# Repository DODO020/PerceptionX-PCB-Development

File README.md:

PerceptionX PCB development repository

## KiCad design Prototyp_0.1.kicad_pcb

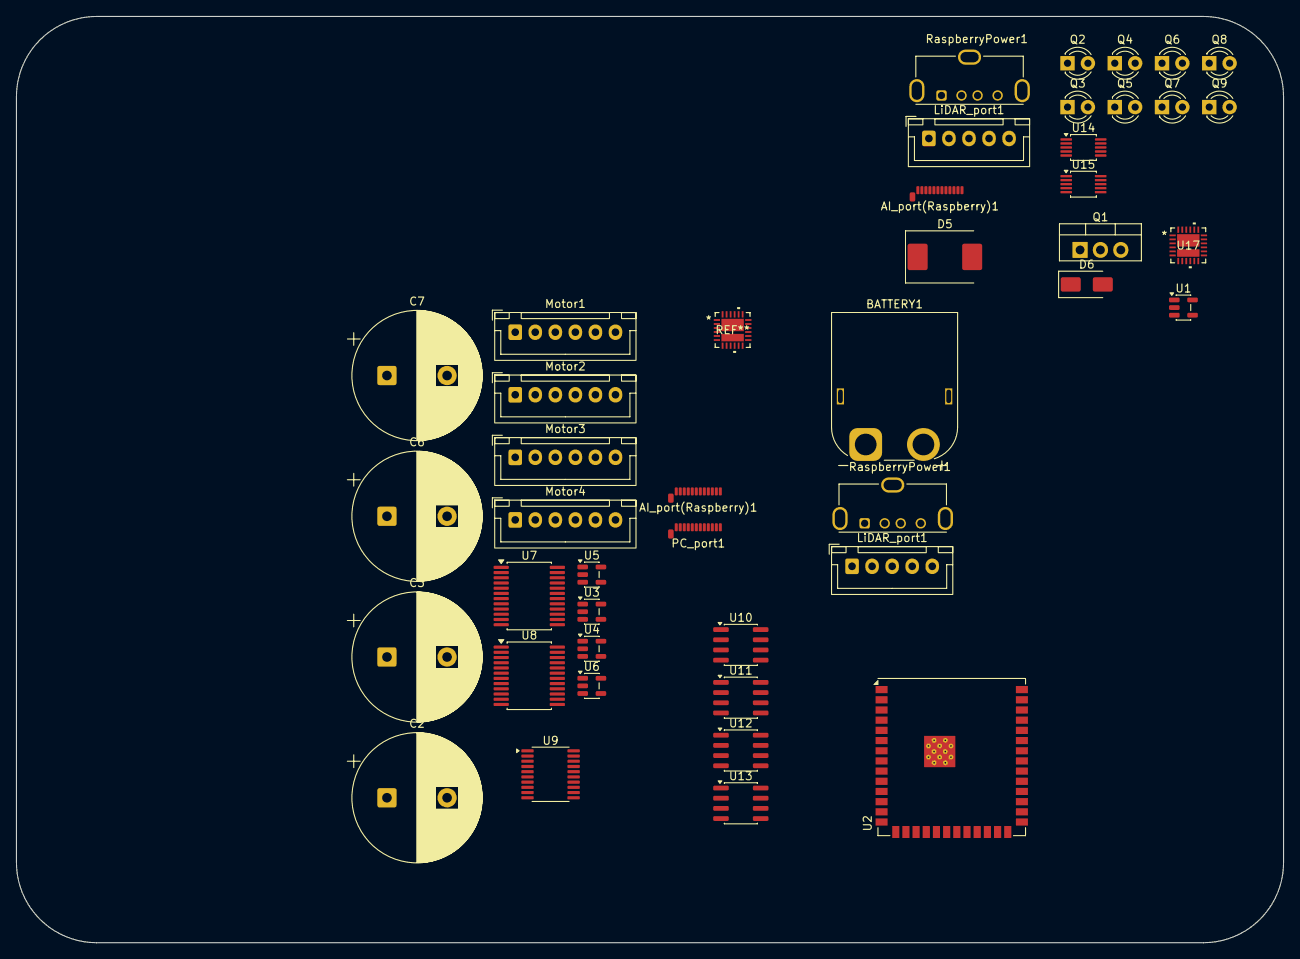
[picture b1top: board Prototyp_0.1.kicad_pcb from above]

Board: 2 copper layers, 158.0 x 115.5 mm, 43 parts (0 on the bottom side), 56 nets, no tracks yet.

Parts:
AI_port(Raspberry)1, AI_port(Raspberry)1#2: USB_C_Plug_USB2.0; USB_C_Plug_Molex_105444
BATTERY1: Conn_01x02; AMASS_XT60PW-M_1x02_P7.20mm_Horizontal
C2, C3: 10uF; CP_Radial_D16.0mm_P7.50mm
C6, C7: 220uF; CP_Radial_D16.0mm_P7.50mm
D5: 1.5SMCxxCA; D_SMC
D6: SS34; D_SMA
LiDAR_port1, LiDAR_port1#2: Conn_01x05; JST_XH_B5B-XH-A_1x05_P2.50mm_Vertical
Motor1, Motor2, Motor3, Motor4: Conn_01x06; JST_XH_B6B-XH-A_1x06_P2.50mm_Vertical
PC_port1: USB_C_Plug_USB2.0; USB_C_Plug_Molex_105444
Q1: IRLB8721PBF; TO-220-3_Vertical
Q2, Q3, Q4, Q5, Q6, Q7, Q8, Q9: SFH309; LED_D3.0mm_Clear
RaspberryPower1, RaspberryPower1#2: USB_A; USB_A_Molex_105057_Vertical
U1: XC6220B331MR; SOT-23-5
U2: ESP32-S3-WROOM-1U
U3, U4, U5, U6: 74LVC1G04; SOT-23-5
U7, U8: TB6612FNG; SSOP-24_5.3x8.2mm_P0.65mm
U9: PCF8574TS; SSOP-20_4.4x6.5mm_P0.65mm
U10, U11, U12, U13: INA240A1D; SOIC-8_3.9x4.9mm_P1.27mm
U14, U15: ADS1115IDGS; TSSOP-10_3x3mm_P0.5mm
U17: TPS25983; VQFN24_RGE_TEX

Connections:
3V3: C2.1, C3.1, Q2.1 (C), Q3.1 (C), Q4.1 (C), Q5.1 (C), Q6.1 (C), Q7.1 (C), Q8.1 (C), Q9.1 (C), U3.5 (VCC), U4.5 (VCC), U5.5 (VCC), U6.5 (VCC), U7.20 (VCC), U8.20 (VCC), U9.5 (VDD), U10.3 (REF2), U10.6 (V+), U11.3 (REF2), U11.6 (V+), U12.3 (REF2), U12.6 (V+), U13.3 (REF2), U13.6 (V+), U14.8 (VDD), U15.1 (ADDR), U15.8 (VDD)
5V: BATTERY1.2, C6.1, C7.1, D5.2 (A2), D6.1 (K), Motor1.4 (BLUE_ENC-VCC), Motor2.4 (BLUE_ENC-VCC), Motor3.4 (BLUE_ENC-VCC), Motor4.4 (BLUE_ENC-VCC), U1.1 (VIN), U7.13 (VM2), U7.14 (VM3), U7.24 (VM1), U8.13 (VM2), U8.14 (VM3), U8.24 (VM1), U17.1 (IN), U17.2 (IN), U17.3 (IN), U17.16 (IN), U17.25 (IN)
12V: U17.17 (OUT), U17.18 (OUT), U17.19 (OUT), U17.20 (OUT), U17.21 (OUT), U17.22 (OUT), U17.23 (OUT), U17.24 (OUT)
/I2C.SCL: U2.38 (IO2), U9.2 (SCL)
/I2C.SDA: U2.39 (IO1), U9.4 (SDA)
/LineSensor/I2C.SCL: U14.10 (SCL), U15.10 (SCL)
/LineSensor/I2C.SDA: U14.9 (SDA), U15.9 (SDA)
/MotorDriver/Motor1DIR: U3.2, U7.22 (AIN2), U9.14 (P3)
/MotorDriver/Motor2DIR: U5.2, U7.16 (BIN2), U9.12 (P2)
/MotorDriver/Motor3DIR: U4.2, U8.22 (AIN2), U9.11 (P1)
/MotorDriver/Motor4DIR: U6.2, U8.16 (BIN2), U9.10 (P0)
/PWM1: U2.20 (IO12), U7.23 (PWMA)
/PWM2: U2.19 (IO11), U7.15 (PWMB)
/PWM3: U2.18 (IO10), U8.23 (PWMA)
/PWM4: U2.17 (IO9), U8.15 (PWMB)
/Ports/LiDAR_RX: LiDAR_port1#2.3 (RX), U2.37 (TXD0)
/Ports/LiDAR_TX: LiDAR_port1#2.4 (TX), U2.36 (RXD0)
/Ports/RPI_D+: AI_port(Raspberry)1.A6 (D+), U2.14 (USB_D+)
/Ports/RPI_D-: AI_port(Raspberry)1.A7 (D-), U2.13 (USB_D-)
/STBY: U2.12 (IO8), U7.19 (STBY), U8.19 (STBY)
GNDA: U10.7 (REF1), U11.7 (REF1), U12.7 (REF1)
GNDD: C2.2, C3.2, LiDAR_port1#2.2 (GND), Motor1.3 (GREEN_ENC-GND), Motor2.3 (GREEN_ENC-GND), Motor3.3 (GREEN_ENC-GND), Motor4.3 (GREEN_ENC-GND), U1.2 (GND), U2.1 (GND), U2.40 (GND), U2.41 (GND), U3.3 (GND), U4.3 (GND), U5.3 (GND), U6.3 (GND), U7.18 (GND), U8.18 (GND), U9.6 (A0), U9.7 (A1), U9.9 (A2), U9.15 (VSS), U10.2 (GND), U10.4 (GND), U11.2 (GND), U11.4 (GND), U12.2 (GND), U12.4 (GND), U13.2 (GND), U13.4 (GND), U14.1 (ADDR), U14.3 (GND), U15.3 (GND), U17.4 (GND), U17.5 (GND), U17.14 (GND), U17.26 (GND)
GNDPWR: C6.2, C7.2, D5.1 (A1), Q1.3 (S), U7.3 (PGND1), U7.4 (PGND1), U7.9 (PGND2), U7.10 (PGND2), U8.3 (PGND1), U8.4 (PGND1), U8.9 (PGND2), U8.10 (PGND2)
unnamed: AI_port(Raspberry)1.A1 (GND), AI_port(Raspberry)1.A12 (GND), AI_port(Raspberry)1.B1 (GND), AI_port(Raspberry)1.B12 (GND), AI_port(Raspberry)1#2.A1 (GND), AI_port(Raspberry)1#2.A12 (GND), AI_port(Raspberry)1#2.B1 (GND), AI_port(Raspberry)1#2.B12 (GND)
unnamed: AI_port(Raspberry)1#2.A4 (VBUS), AI_port(Raspberry)1#2.A9 (VBUS), AI_port(Raspberry)1#2.B4 (VBUS), AI_port(Raspberry)1#2.B9 (VBUS)
unnamed: U1.5 (VOUT), U2.2 (3V3), U2.3 (EN)
unnamed: D6.2 (A), Q1.2 (D)
unnamed: AI_port(Raspberry)1.A4 (VBUS), AI_port(Raspberry)1.A9 (VBUS), AI_port(Raspberry)1.B4 (VBUS), AI_port(Raspberry)1.B9 (VBUS), LiDAR_port1#2.5 (VCC), RaspberryPower1.1 (VBUS_1)
unnamed: Motor1.2 (BLACK_MOTOR), U7.5 (AO2), U7.6 (AO2)
unnamed: Motor1.1 (RED_MOTOR), U10.1 (-)
unnamed: Motor2.2 (BLACK_MOTOR), U7.7 (BO2), U7.8 (BO2)
unnamed: Motor2.1 (RED_MOTOR), U11.1 (-)
unnamed: Motor3.2 (BLACK_MOTOR), U8.5 (AO2), U8.6 (AO2)
unnamed: Motor3.1 (RED_MOTOR), U12.1 (-)
unnamed: Motor4.2 (BLACK_MOTOR), U8.7 (BO2), U8.8 (BO2)
unnamed: Motor4.1 (RED_MOTOR), U13.1 (-)
unnamed: PC_port1.A6 (D+), RaspberryPower1#2.3 (D+)
unnamed: PC_port1.A7 (D-), RaspberryPower1#2.2 (D-)
unnamed: PC_port1.A1 (GND), PC_port1.A12 (GND), PC_port1.B1 (GND), PC_port1.B12 (GND)
unnamed: PC_port1.A4 (VBUS), PC_port1.A9 (VBUS), PC_port1.B4 (VBUS), PC_port1.B9 (VBUS)
unnamed: Q2.2 (E), U14.4 (AIN0)
unnamed: Q3.2 (E), U14.6 (AIN2)
unnamed: Q4.2 (E), U14.7 (AIN3)
unnamed: Q5.2 (E), U14.5 (AIN1)
unnamed: Q6.2 (E), U15.4 (AIN0)
unnamed: Q7.2 (E), U15.5 (AIN1)
unnamed: Q8.2 (E), U15.6 (AIN2)
unnamed: Q9.2 (E), U15.7 (AIN3)
unnamed: U3.4, U7.21 (AIN1)
unnamed: U5.4, U7.17 (BIN1)
unnamed: U4.4, U8.21 (AIN1)
unnamed: U6.4, U8.17 (BIN1)
unnamed: U7.1 (AO1), U7.2 (AO1), U10.8 (+)
unnamed: U7.11 (BO1), U7.12 (BO1), U11.8 (+)
unnamed: U8.1 (AO1), U8.2 (AO1), U12.8 (+)
unnamed: U8.11 (BO1), U8.12 (BO1), U13.8 (+)

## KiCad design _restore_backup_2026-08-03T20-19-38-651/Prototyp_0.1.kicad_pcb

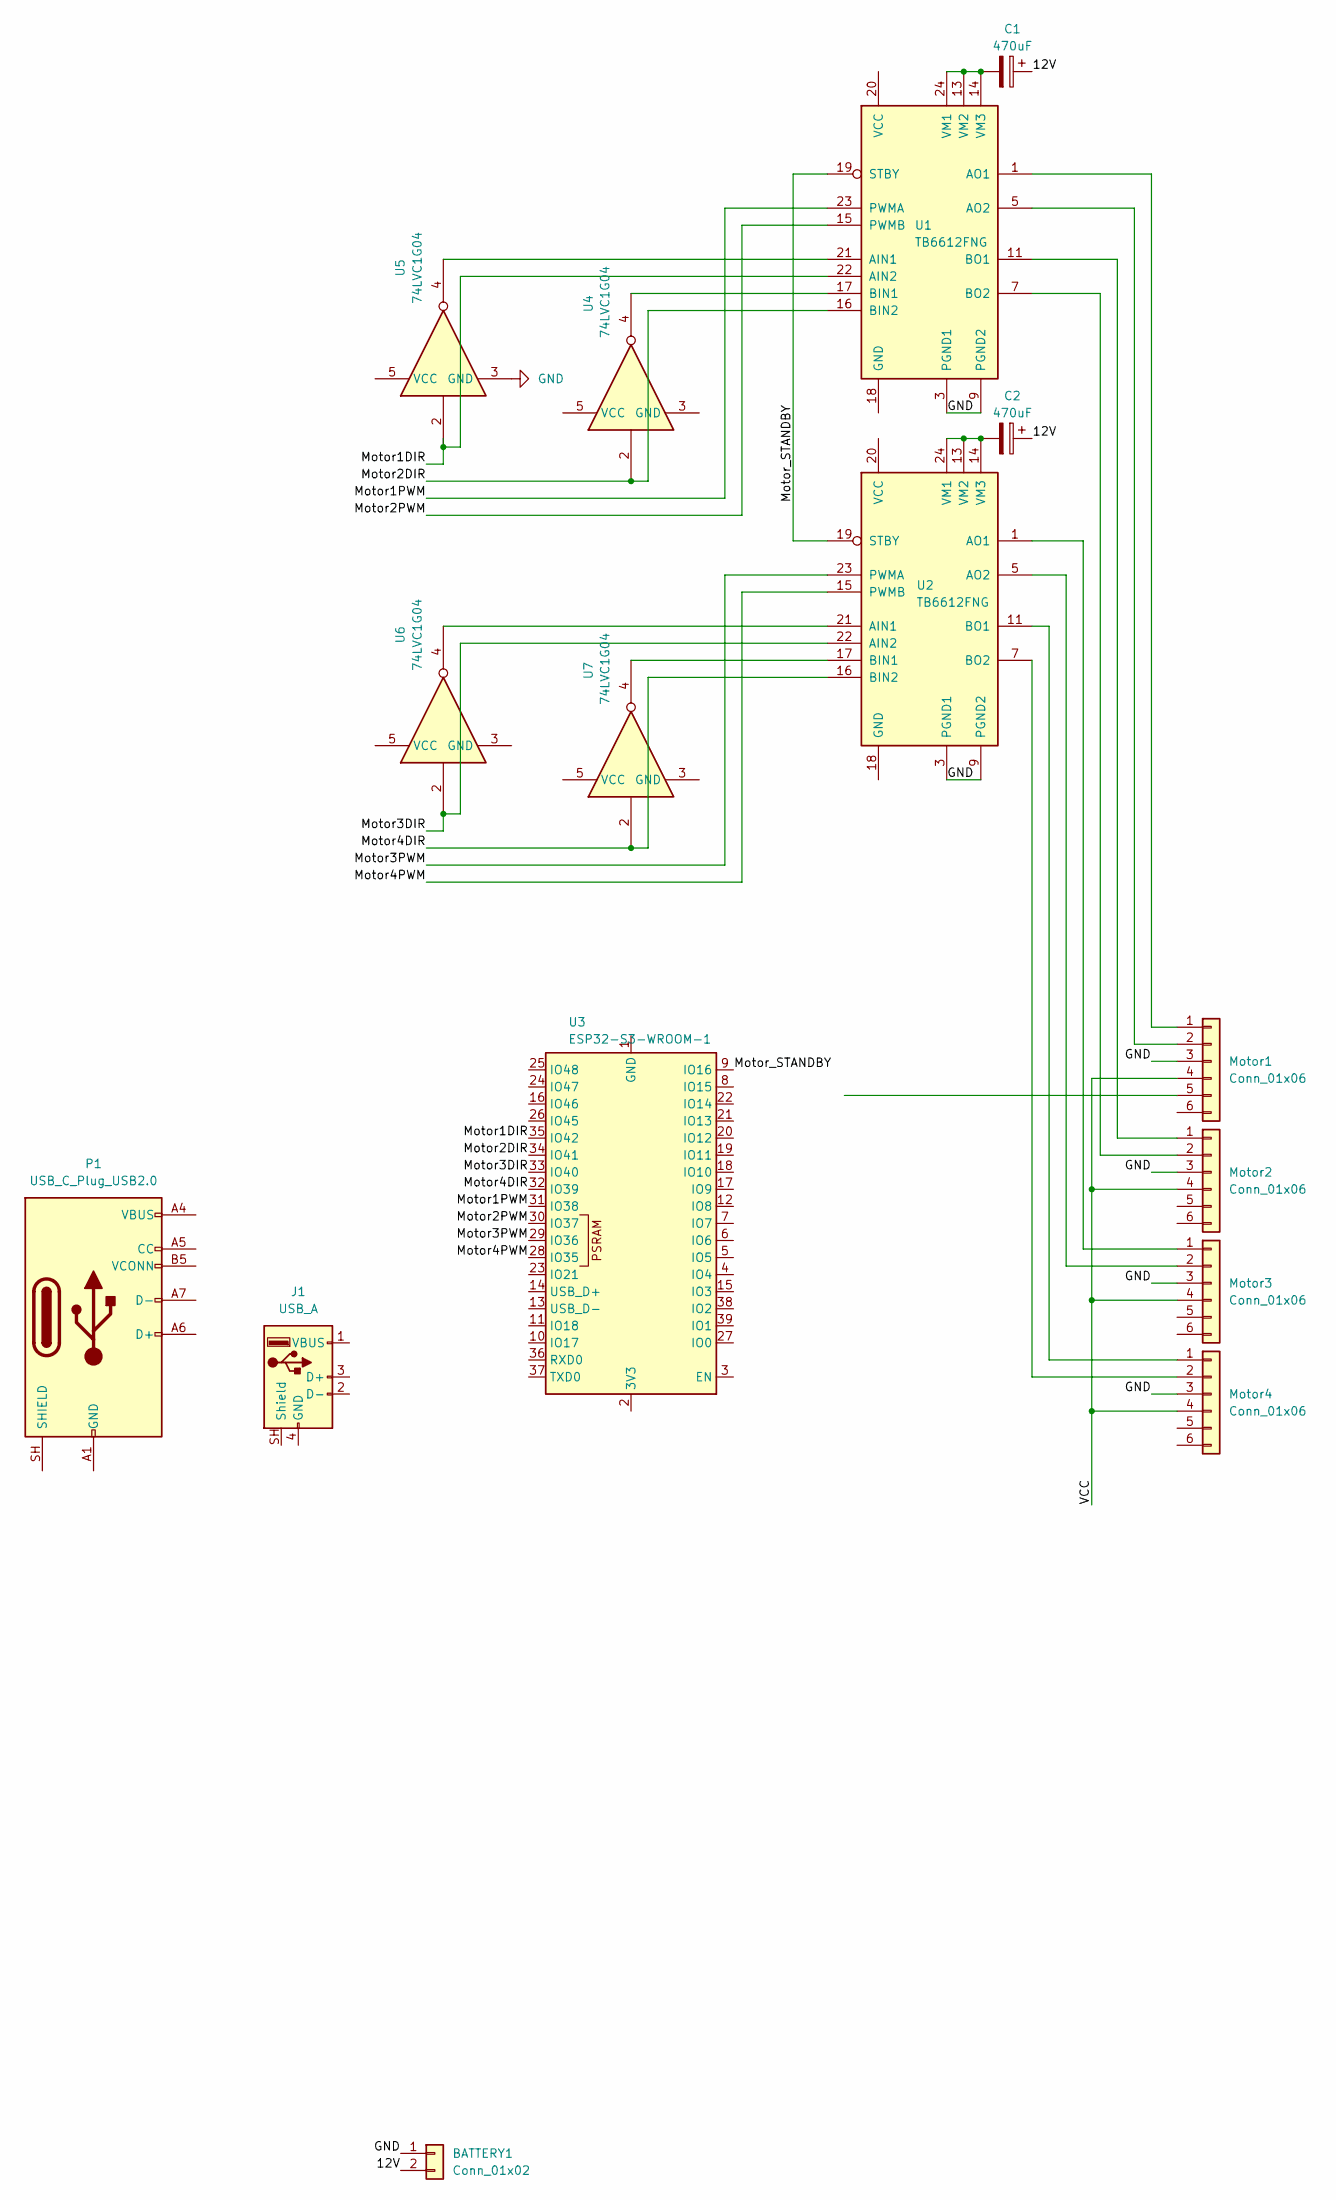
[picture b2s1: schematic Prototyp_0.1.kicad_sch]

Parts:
BATTERY1: Conn_01x02; AMASS_XT60-M_1x02_P7.20mm_Vertical
C1, C2: 470uF; CP_Radial_D16.0mm_P7.50mm
J1: USB_A; USB_A_Molex_105057_Vertical
Motor1, Motor2, Motor3, Motor4: Conn_01x06; JST_PH_B6B-PH-SM4-TB_1x06-1MP_P2.00mm_Vertical
P1: USB_C_Plug_USB2.0; USB_C_Plug_Molex_105444
U1, U2: TB6612FNG; SSOP-24_5.3x8.2mm_P0.65mm
U3: ESP32-S3-WROOM-1
U4, U5, U6, U7: 74LVC1G04; SOT-23-5

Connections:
/5V: U4.5 (VCC), U5.5 (VCC), U6.5 (VCC), U7.5 (VCC)
/12V: BATTERY1.2, C1.1, C2.1
/GND: BATTERY1.1, Motor1.3 (GREEN_ENC-GND), Motor2.3 (GREEN_ENC-GND), Motor3.3 (GREEN_ENC-GND), Motor4.3 (GREEN_ENC-GND), U1.3 (PGND1), U1.4 (PGND1), U1.9 (PGND2), U1.10 (PGND2), U2.3 (PGND1), U2.4 (PGND1), U2.9 (PGND2), U2.10 (PGND2), U4.3 (GND), U5.3 (GND), U6.3 (GND), U7.3 (GND)
/Motor1DIR: U1.22 (AIN2), U3.35 (IO42), U5.2
/Motor1PWM: U1.23 (PWMA), U3.31 (IO38)
/Motor2DIR: U1.16 (BIN2), U3.34 (IO41), U4.2
/Motor2PWM: U1.15 (PWMB), U3.30 (IO37)
/Motor3DIR: U2.22 (AIN2), U3.33 (IO40), U6.2
/Motor3PWM: U2.23 (PWMA), U3.29 (IO36)
/Motor4DIR: U2.16 (BIN2), U3.32 (IO39), U7.2
/Motor4PWM: U2.15 (PWMB), U3.28 (IO35)
/Motor_STANDBY: U1.19 (STBY), U2.19 (STBY), U3.9 (IO16)
/VCC: Motor1.4 (BLUE_ENC-VCC), Motor2.4 (BLUE_ENC-VCC), Motor3.4 (BLUE_ENC-VCC), Motor4.4 (BLUE_ENC-VCC)
unnamed: Motor1.2 (BLACK_MOTOR), U1.5 (AO2), U1.6 (AO2)
unnamed: Motor1.1 (RED_MOTOR), U1.1 (AO1), U1.2 (AO1)
unnamed: Motor2.2 (BLACK_MOTOR), U1.7 (BO2), U1.8 (BO2)
unnamed: Motor2.1 (RED_MOTOR), U1.11 (BO1), U1.12 (BO1)
unnamed: Motor3.2 (BLACK_MOTOR), U2.5 (AO2), U2.6 (AO2)
unnamed: Motor3.1 (RED_MOTOR), U2.1 (AO1), U2.2 (AO1)
unnamed: Motor4.2 (BLACK_MOTOR), U2.7 (BO2), U2.8 (BO2)
unnamed: Motor4.1 (RED_MOTOR), U2.11 (BO1), U2.12 (BO1)
unnamed: P1.A1 (GND), P1.A12 (GND), P1.B1 (GND), P1.B12 (GND)
unnamed: P1.A4 (VBUS), P1.A9 (VBUS), P1.B4 (VBUS), P1.B9 (VBUS)
unnamed: U1.21 (AIN1), U5.4
unnamed: U1.17 (BIN1), U4.4
unnamed: C1.2, U1.13 (VM2), U1.14 (VM3), U1.24 (VM1)
unnamed: U2.21 (AIN1), U6.4
unnamed: U2.17 (BIN1), U7.4
unnamed: C2.2, U2.13 (VM2), U2.14 (VM3), U2.24 (VM1)
unnamed: U3.1 (GND), U3.40 (GND), U3.41 (GND)

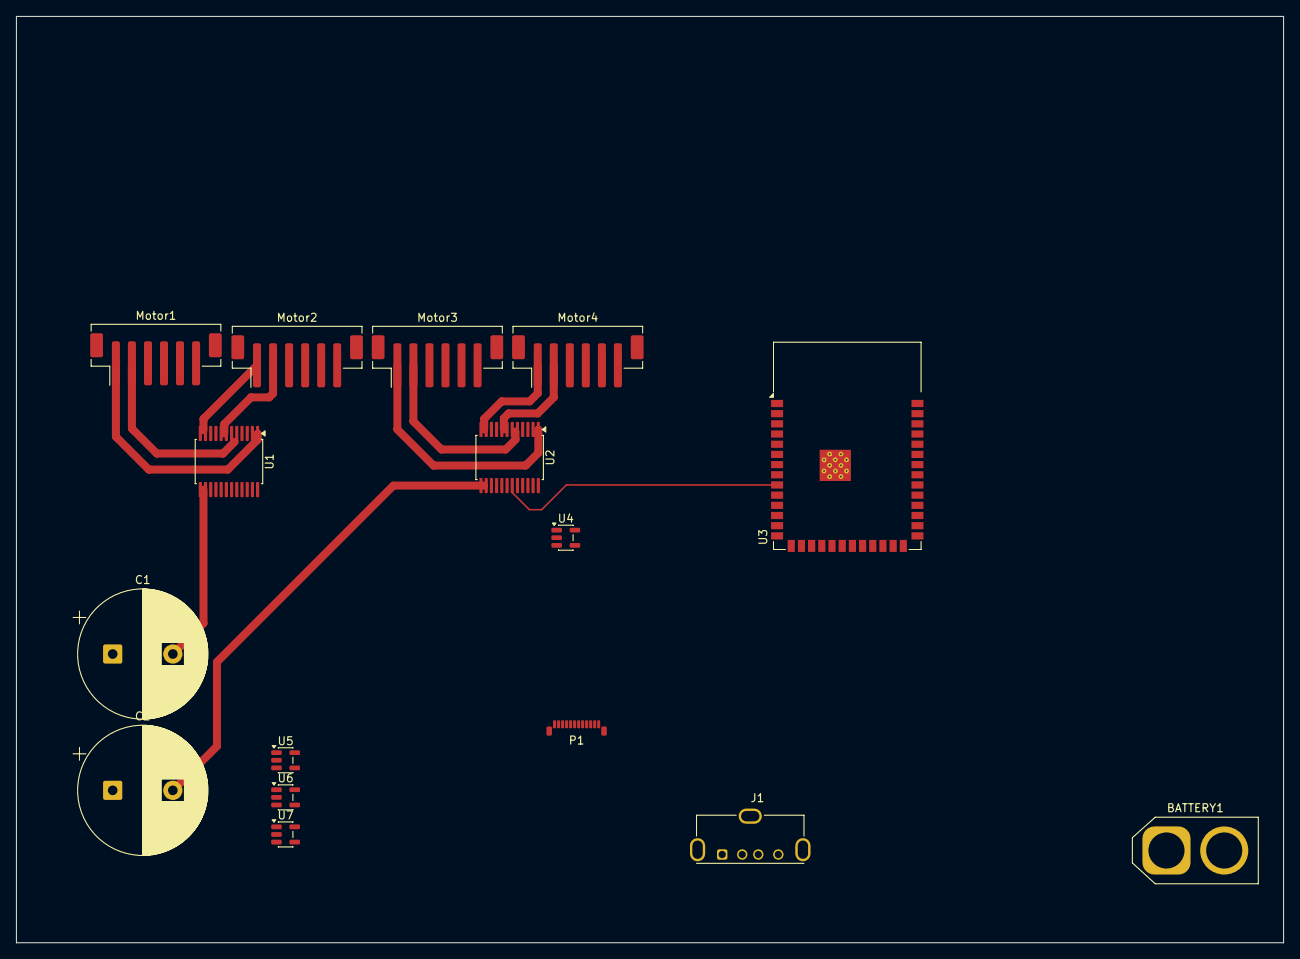
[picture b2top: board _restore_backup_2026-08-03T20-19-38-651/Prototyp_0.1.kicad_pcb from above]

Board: 2 copper layers, 158.0 x 115.5 mm, 16 parts (0 on the bottom side), 30 nets.
